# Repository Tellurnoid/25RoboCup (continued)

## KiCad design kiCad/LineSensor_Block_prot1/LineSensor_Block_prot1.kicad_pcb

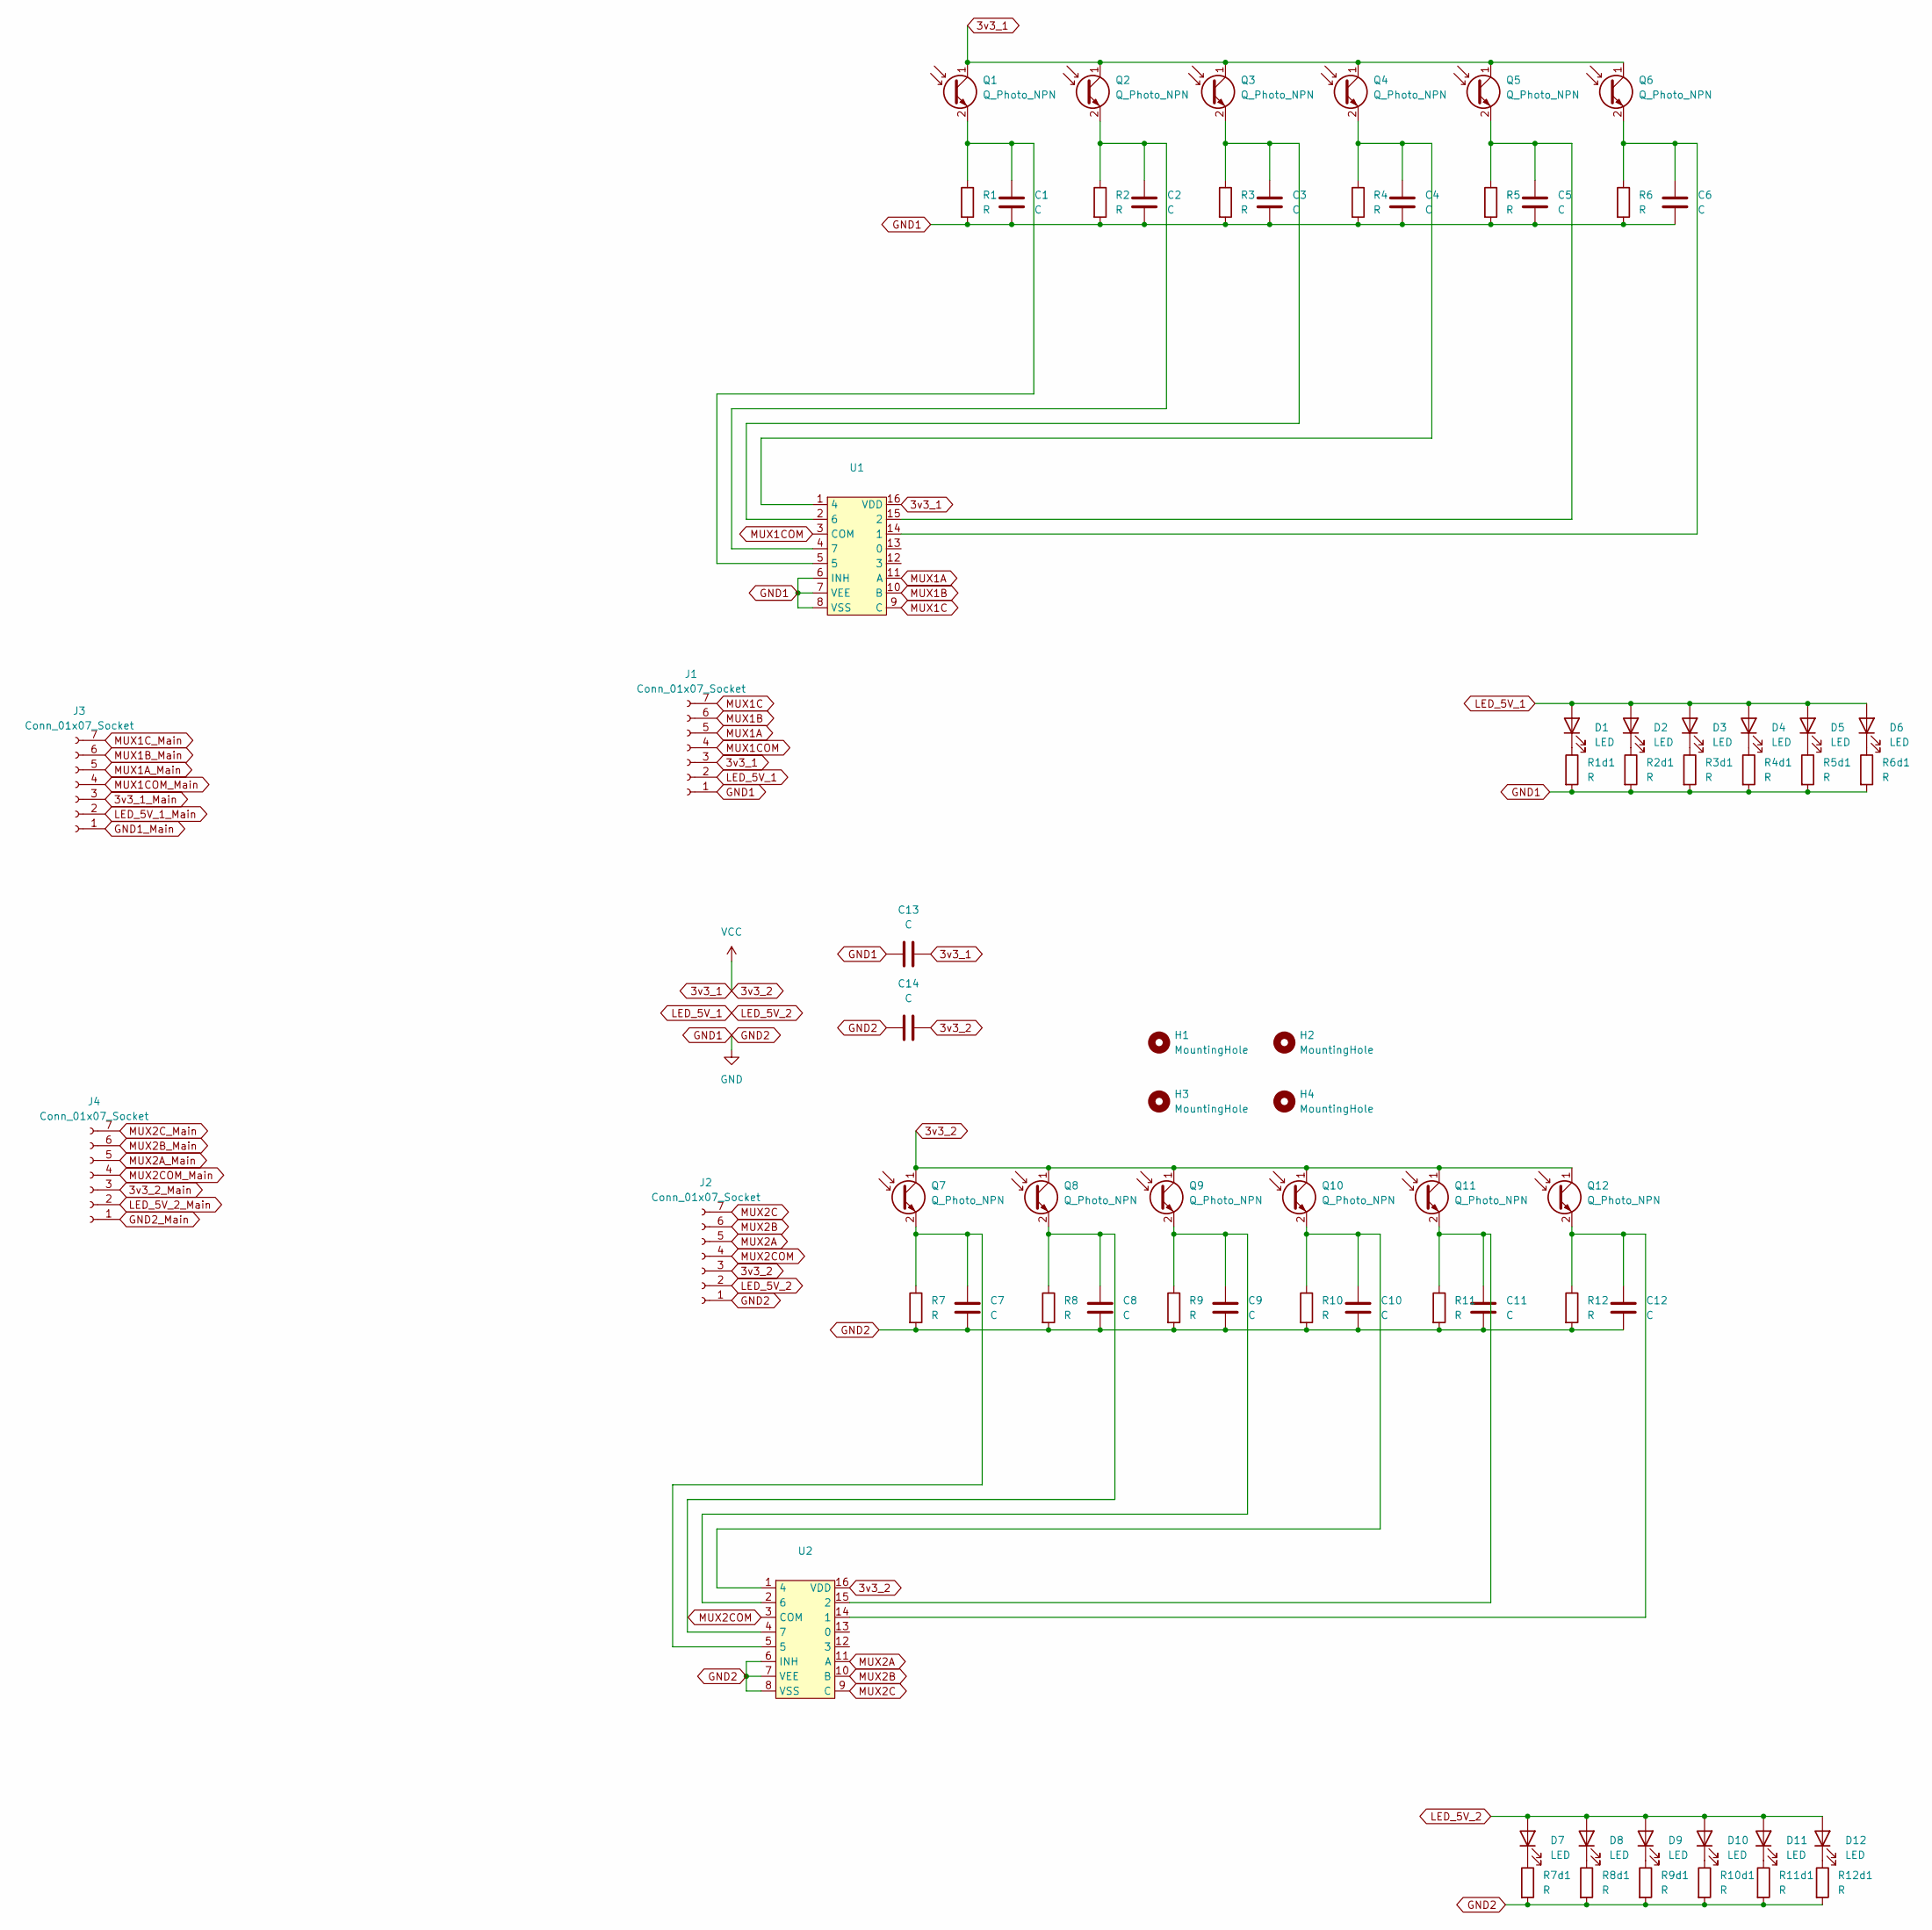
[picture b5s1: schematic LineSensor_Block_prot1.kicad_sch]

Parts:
C1, C2, C3, C4, C5, C6, C8, C9, C10, C11, C12, C13, C14: C; C_0603_1608Metric
C7: C; R_0603_1608Metric
D1, D2, D3, D4, D5, D6, D7, D8, D9, D10, D11, D12: LED; LED_0603_1608Metric
H1, H2, H3, H4: MountingHole; MountingHole_3.2mm_M3
J1, J2: Conn_01x07_Socket; PinHeader_1x07_P2.54mm_Horizontal_edited
J3, J4: Conn_01x07_Socket; PinSocket_1x07_P2.54mm_Horizontal_edited
Q1, Q2, Q3, Q4, Q5, Q6, Q7, Q8, Q9, Q10, Q11, Q12: Q_Photo_NPN; LED_0603_1608Metric
R1, R1d1, R2, R2d1, R3, R3d1, R4, R4d1, R5, R5d1, R6, R6d1, R7, R7d1, R8, R8d1, R9, R9d1, R10, R10d1, R11, R11d1, R12, R12d1: R; R_0603_1608Metric
U1, U2: TSSOP-16_4.4x5mm_P0.65mm

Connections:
3v3_1: C13.2, C14.2, J1.3, J2.3, Q1.1 (C), Q2.1 (C), Q3.1 (C), Q4.1 (C), Q5.1 (C), Q6.1 (C), Q7.1 (C), Q8.1 (C), Q9.1 (C), Q10.1 (C), Q11.1 (C), Q12.1 (C), U1.16 (VDD), U2.16 (VDD)
3v3_1_Main: J3.3
3v3_2_Main: J4.3
GND1: C1.2, C2.2, C3.2, C4.2, C5.2, C6.2, C7.2, C8.2, C9.2, C10.2, C11.2, C12.2, C13.1, C14.1, J1.1, J2.1, R1.2, R1d1.2, R2.2, R2d1.2, R3.2, R3d1.2, R4.2, R4d1.2, R5.2, R5d1.2, R6.2, R6d1.2, R7.2, R7d1.2, R8.2, R8d1.2, R9.2, R9d1.2, R10.2, R10d1.2, R11.2, R11d1.2, R12.2, R12d1.2, U1.6 (INH), U1.7 (VEE), U1.8 (VSS), U2.6 (INH), U2.7 (VEE), U2.8 (VSS)
GND1_Main: J3.1
GND2_Main: J4.1
LED_5V_1: D1.2 (A), D2.2 (A), D3.2 (A), D4.2 (A), D5.2 (A), D6.2 (A), D7.2 (A), D8.2 (A), D9.2 (A), D10.2 (A), D11.2 (A), D12.2 (A), J1.2, J2.2
LED_5V_1_Main: J3.2
LED_5V_2_Main: J4.2
MUX1A: J1.5, U1.11 (A)
MUX1A_Main: J3.5
MUX1B: J1.6, U1.10 (B)
MUX1B_Main: J3.6
MUX1C: J1.7, U1.9 (C)
MUX1COM: J1.4, U1.3 (COM)
MUX1COM_Main: J3.4
MUX1C_Main: J3.7
MUX2A: J2.5, U2.11 (A)
MUX2A_Main: J4.5
MUX2B: J2.6, U2.10 (B)
MUX2B_Main: J4.6
MUX2C: J2.7, U2.9 (C)
MUX2COM: J2.4, U2.3 (COM)
MUX2COM_Main: J4.4
MUX2C_Main: J4.7
unnamed: D1.1 (K), R1d1.1
unnamed: D2.1 (K), R2d1.1
unnamed: D3.1 (K), R3d1.1
unnamed: D4.1 (K), R4d1.1
unnamed: D5.1 (K), R5d1.1
unnamed: D6.1 (K), R6d1.1
unnamed: D7.1 (K), R7d1.1
unnamed: D8.1 (K), R8d1.1
unnamed: D9.1 (K), R9d1.1
unnamed: D10.1 (K), R10d1.1
unnamed: D11.1 (K), R11d1.1
unnamed: D12.1 (K), R12d1.1
unnamed: C1.1, Q1.2 (E), R1.1, U1.5
unnamed: C2.1, Q2.2 (E), R2.1, U1.4 (7)
unnamed: C3.1, Q3.2 (E), R3.1, U1.2 (6)
unnamed: C4.1, Q4.2 (E), R4.1, U1.1 (4)
unnamed: C5.1, Q5.2 (E), R5.1, U1.15 (2)
unnamed: C6.1, Q6.2 (E), R6.1, U1.14 (1)
unnamed: C7.1, Q7.2 (E), R7.1, U2.5
unnamed: C8.1, Q8.2 (E), R8.1, U2.4 (7)
unnamed: C9.1, Q9.2 (E), R9.1, U2.2 (6)
unnamed: C10.1, Q10.2 (E), R10.1, U2.1 (4)
unnamed: C11.1, Q11.2 (E), R11.1, U2.15 (2)
unnamed: C12.1, Q12.2 (E), R12.1, U2.14 (1)

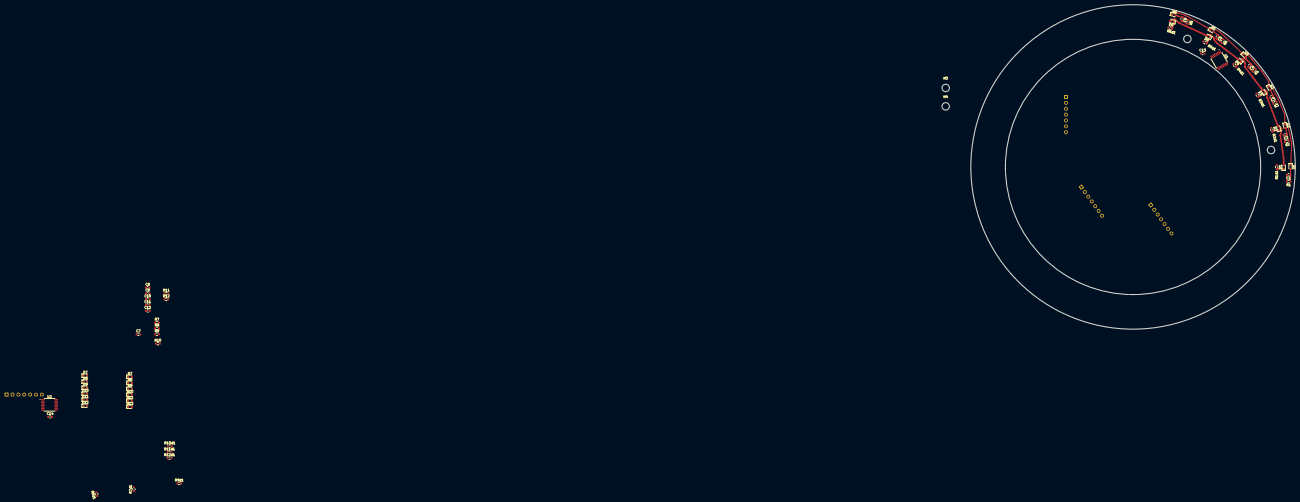
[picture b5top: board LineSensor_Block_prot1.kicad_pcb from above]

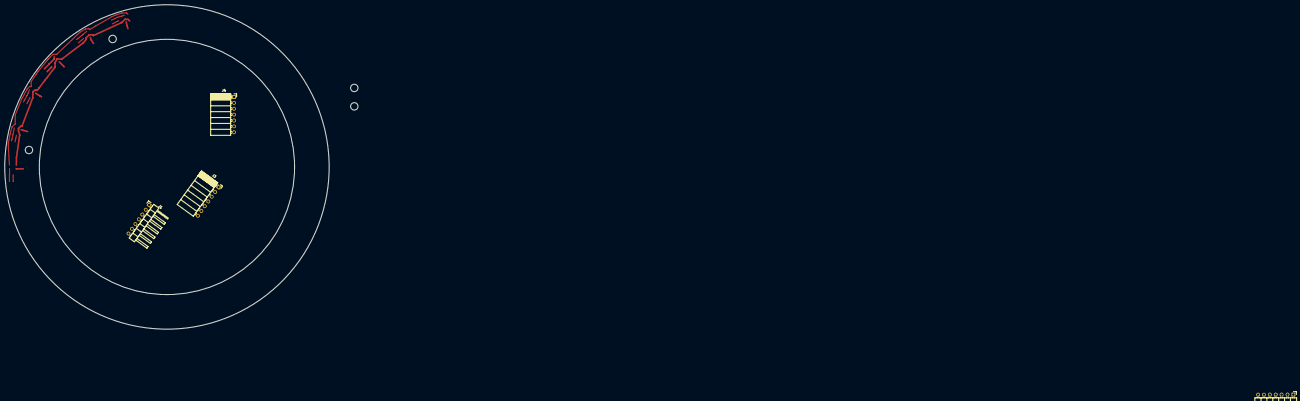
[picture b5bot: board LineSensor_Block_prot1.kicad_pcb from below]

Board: 2 copper layers, 140.0 x 140.0 mm, 72 parts (4 on the bottom side), 35 nets.

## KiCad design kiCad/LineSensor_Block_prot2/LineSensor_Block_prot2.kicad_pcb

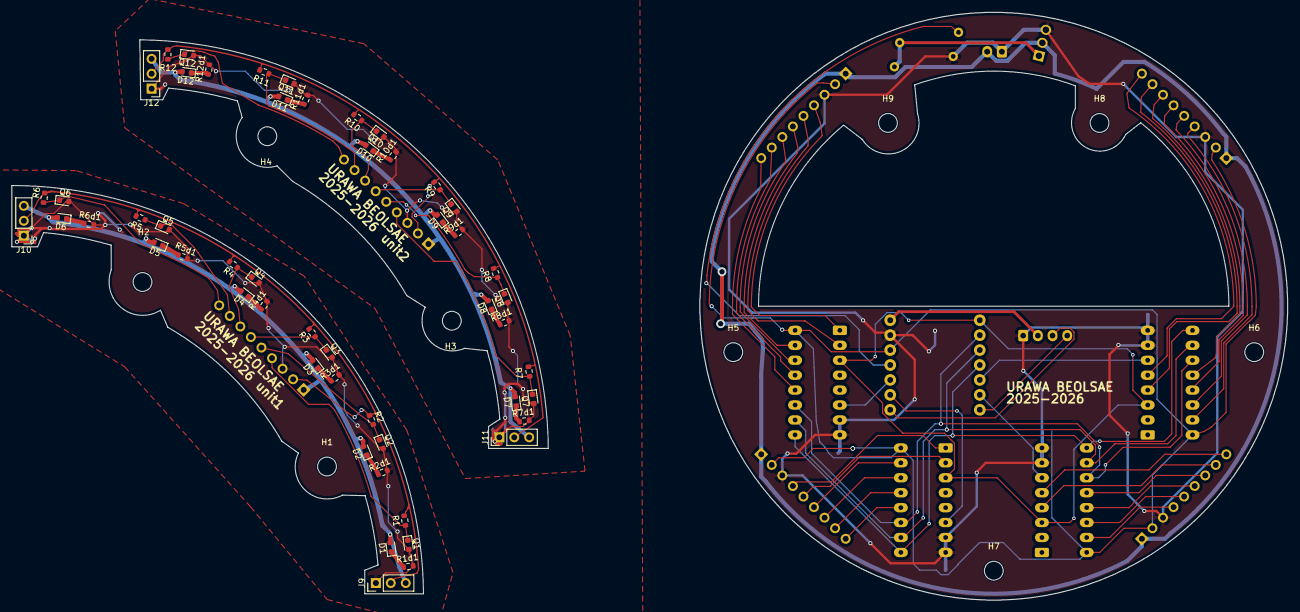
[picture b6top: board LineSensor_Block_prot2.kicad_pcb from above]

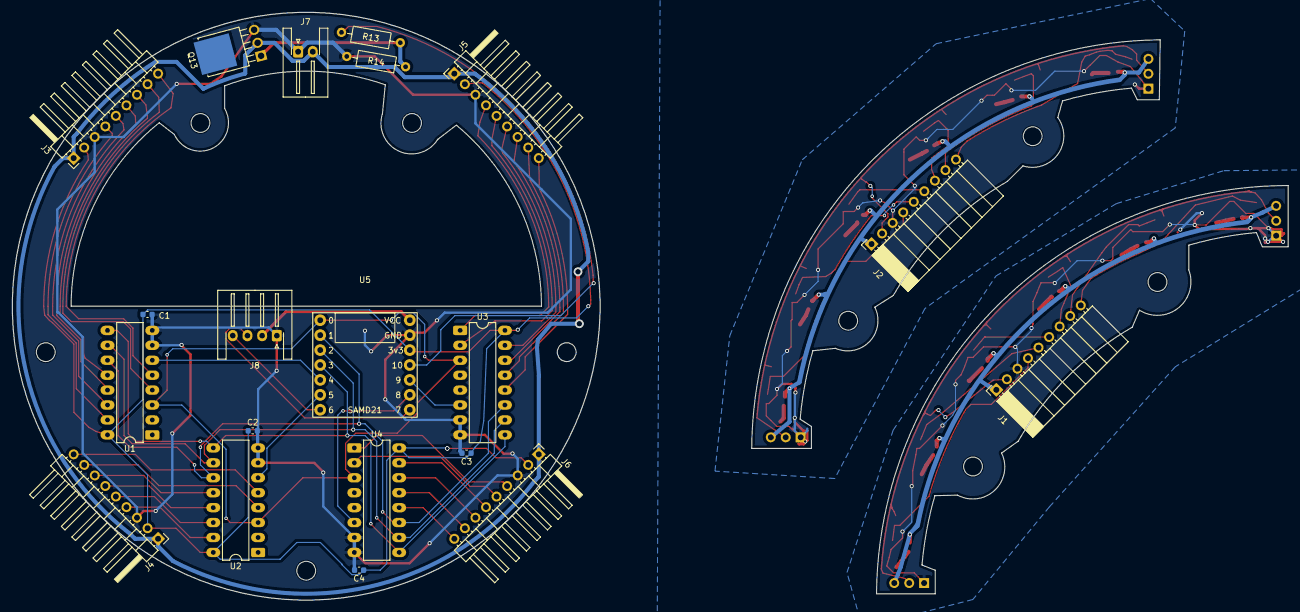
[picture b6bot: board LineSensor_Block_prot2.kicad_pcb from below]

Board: 2 copper layers, 217.1 x 100.0 mm, 81 parts (20 on the bottom side), 70 nets.

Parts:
C1, C2, C3, C4: C; C_0603_1608Metric
D1, D2, D3, D4, D5, D6, D7, D8, D9, D10, D11, D12: LED; LED_0603_1608Metric
H1, H2, H3, H4, H5, H6, H7, H8, H9: MountingHole; MountingHole_3.2mm_M3
J1, J2: Conn_01x09_Socket; PinSocket_1x09_P2.54mm_Horizontal_EDITED
J3, J4, J5, J6: Conn_01x09_Socket; PinHeader_1x09_P2.54mm_Horizontal_EDITED
J7: Conn_01x02_Socket; JST_XH_S2B-XH-A-1_1x02_P2.50mm_Horizontal
J8: Conn_01x04_Socket; JST_XH_S4B-XH-A-1_1x04_P2.50mm_Horizontal
J9, J10, J11, J12: Conn_01x03_Socket; PinHeader_1x03_P2.54mm_Vertical_EDITED
Q1, Q2, Q3, Q4, Q5, Q6, Q7, Q8, Q9, Q10, Q11, Q12: Q_Photo_NPN; LED_0603_1608Metric
Q13: NMOS; TO-251-3-1EP_Horizontal_TabDown
R1, R1d1, R2, R2d1, R3, R3d1, R4, R4d1, R5, R5d1, R6, R6d1, R7, R7d1, R8, R8d1, R9, R9d1, R10, R10d1, R11, R11d1, R12, R12d1: R; R_0603_1608Metric
R13, R14: R; R_Axial_DIN0207_L6.3mm_D2.5mm_P10.16mm_Horizontal
U1, U2, U3, U4: 4051; CERDIP-16_W7.62mm_SideBrazed_LongPads_pin_EDITED
U5: 名称未設定

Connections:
3v3_1: J1.2, J9.2, J10.2, R1.1, R2.1, R3.1, R4.1, R5.1, R6.1
3v3_2: J2.2, J11.2, J12.2, R7.1, R8.1, R9.1, R10.1, R11.1, R12.1
GND: C1.2, C2.2, C3.2, C4.2, J3.3, J4.3, J5.3, J6.3, J7.1, J8.1, Q13.3 (S), R14.2, U1.7 (VEE), U1.8 (VSS), U2.7 (VEE), U2.8 (VSS), U3.7 (VEE), U3.8 (VSS), U4.7 (VEE), U4.8 (VSS), U5.13 (GND)
GND1: J1.3, J9.1, J10.1, Q1.2 (E), Q2.2 (E), Q3.2 (E), Q4.2 (E), Q5.2 (E), Q6.2 (E), R1d1.2, R2d1.2, R3d1.2, R4d1.2, R5d1.2, R6d1.2
GND2: J2.3, J11.1, J12.1, Q7.2 (E), Q8.2 (E), Q9.2 (E), Q10.2 (E), Q11.2 (E), Q12.2 (E), R7d1.2, R8d1.2, R9d1.2, R10d1.2, R11d1.2, R12d1.2
LED_5V: J3.1, J4.1, J5.1, J6.1, J7.2, Q13.1 (D)
LED_5V_1: D1.2 (A), D2.2 (A), D3.2 (A), D4.2 (A), D5.2 (A), D6.2 (A), J1.1, J9.3, J10.3
LED_5V_2: D7.2 (A), D8.2 (A), D9.2 (A), D10.2 (A), D11.2 (A), D12.2 (A), J2.1, J11.3, J12.3
unnamed: D1.1 (K), R1d1.1
unnamed: D2.1 (K), R2d1.1
unnamed: D3.1 (K), R3d1.1
unnamed: D4.1 (K), R4d1.1
unnamed: D5.1 (K), R5d1.1
unnamed: D6.1 (K), R6d1.1
unnamed: D7.1 (K), R7d1.1
unnamed: D8.1 (K), R8d1.1
unnamed: D9.1 (K), R9d1.1
unnamed: D10.1 (K), R10d1.1
unnamed: D11.1 (K), R11d1.1
unnamed: D12.1 (K), R12d1.1
unnamed: J1.4, Q1.1 (C), R1.2
unnamed: J1.5, Q2.1 (C), R2.2
unnamed: J1.6, Q3.1 (C), R3.2
unnamed: J1.7, Q4.1 (C), R4.2
unnamed: J1.8, Q5.1 (C), R5.2
unnamed: J1.9, Q6.1 (C), R6.2
unnamed: J2.4, Q7.1 (C), R7.2
unnamed: J2.5, Q8.1 (C), R8.2
unnamed: J2.6, Q9.1 (C), R9.2
unnamed: J2.7, Q10.1 (C), R10.2
unnamed: J2.8, Q11.1 (C), R11.2
unnamed: J2.9, Q12.1 (C), R12.2
unnamed: J3.4, U1.15 (X2)
unnamed: J3.5, U1.14 (X1)
unnamed: J3.6, U1.13 (X0)
unnamed: J3.7, U1.12 (X3)
unnamed: J3.8, U1.4 (X7)
unnamed: J3.9, U1.5 (X5)
unnamed: J4.4, U2.15 (X2)
unnamed: J4.5, U2.14 (X1)
unnamed: J4.6, U2.13 (X0)
unnamed: J4.7, U2.12 (X3)
unnamed: J4.8, U2.4 (X7)
unnamed: J4.9, U2.5 (X5)
unnamed: J5.4, U3.1 (X4)
unnamed: J5.5, U3.2 (X6)
unnamed: J5.6, U3.15 (X2)
unnamed: J5.7, U3.14 (X1)
unnamed: J5.8, U3.13 (X0)
unnamed: J5.9, U3.12 (X3)
unnamed: J6.4, U4.1 (X4)
unnamed: J6.5, U4.2 (X6)
unnamed: J6.6, U4.15 (X2)
unnamed: J6.7, U4.14 (X1)
unnamed: J6.8, U4.13 (X0)
unnamed: J6.9, U4.12 (X3)
unnamed: Q13.2 (G), R13.1, R14.1
unnamed: U1.11 (A), U2.11 (A), U3.11 (A), U4.11 (A), U5.2 (1)
unnamed: U1.10 (B), U2.10 (B), U3.10 (B), U4.10 (B), U5.3 (2)
unnamed: U1.9 (C), U2.9 (C), U3.9 (C), U4.9 (C), U5.4 (3)
unnamed: U1.6 (Inh), U5.5 (4)
unnamed: U1.3 (X), U2.3 (X), U3.3 (X), U4.3 (X), U5.1 (0)
unnamed: U2.6 (Inh), U5.6 (5)
unnamed: U3.6 (Inh), U5.10 (9)
unnamed: U4.6 (Inh), U5.9 (8)
unnamed: R13.2, U5.11 (10)
RX: J8.3, U5.8 (7)
TX: J8.4, U5.7 (6)
VCC: J8.2, U5.14 (VCC)
seed_3v3: C1.1, C2.1, C3.1, C4.1, J3.2, J4.2, J5.2, J6.2, U1.16 (VDD), U2.16 (VDD), U3.16 (VDD), U4.16 (VDD), U5.12 (3v3)

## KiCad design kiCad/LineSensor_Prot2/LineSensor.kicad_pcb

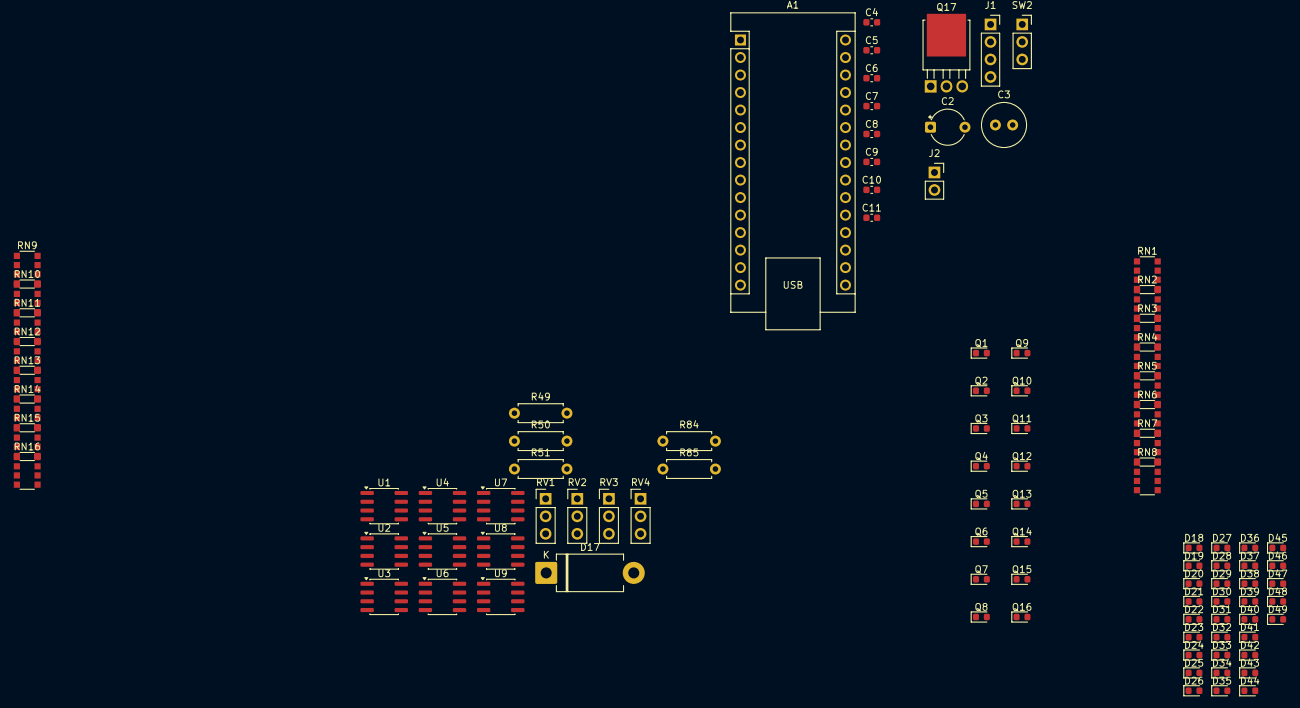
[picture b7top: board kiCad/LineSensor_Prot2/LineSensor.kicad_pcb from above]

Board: 2 copper layers, 98 parts (0 on the bottom side), 78 nets, no tracks yet.

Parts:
A1: Arduino_Nano_v2.x; Arduino_Nano
C2: C; CP_Radial_Tantal_D5.0mm_P5.00mm
C3: C; C_Radial_D6.3mm_H11.0mm_P2.50mm
C4, C5, C6, C7, C8, C9, C10, C11: C; C_0603_1608Metric
D17: D; D_DO-201AD_P12.70mm_Horizontal
D18, D19, D20, D21, D22, D23, D24, D25, D26, D27, D28, D29, D30, D31, D32, D33, D34, D35, D36, D37, D38, D39, D40, D41, D42, D43, D44, D45, D46, D47, D48, D49: LED; LED_0603_1608Metric
J1: Conn_01x04_Socket; PinSocket_1x04_P2.54mm_Vertical
J2: Conn_01x02_Socket; PinSocket_1x02_P2.54mm_Vertical
Q1, Q2, Q3, Q4, Q5, Q6, Q7, Q8, Q9, Q10, Q11, Q12, Q13, Q14, Q15, Q16: Q_Photo_NPN; LED_0603_1608Metric
Q17: NMOS; TO-251-3-1EP_Horizontal_TabDown
R49, R50, R51, R84, R85: R; R_Axial_DIN0207_L6.3mm_D2.5mm_P7.62mm_Horizontal
RN1, RN2, RN3, RN4, RN5, RN6, RN7, RN8, RN9, RN10, RN11, RN12, RN13, RN14, RN15, RN16: R_Network04; R_Array_Convex_4x1206
RV1, RV2, RV3, RV4: R_Potentiometer_Trim; PinHeader_1x03_P2.54mm_Vertical
SW2: SW_DPST_x2; PinSocket_1x03_P2.54mm_Vertical
U1, U2, U3, U4, U5, U6, U7, U8, U9: LM393; SOIC-8_3.9x4.9mm_P1.27mm

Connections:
GND: A1.4 (GND), A1.29 (GND), C2.1, C3.2, C4.2, C5.2, C6.2, C7.2, C8.2, C9.2, C10.2, C11.2, D17.1 (K), J1.3, J2.2, Q17.3 (S), R50.2, R85.1, RN13.1 (common), RN14.1 (common), RN15.1 (common), RN16.1 (common), RV1.3, RV2.3, RV3.3, RV4.3, U2.8 (V+), U3.8 (V+), U4.8 (V+), U5.8 (V+), U6.4 (V-), U7.4 (V-), U8.4 (V-), U9.4 (V-)
unnamed: A1.19 (A0), RN10.5 (R4), U8.7
unnamed: A1.20 (A1), RN10.4 (R3), U8.1
unnamed: A1.21 (A2), RN10.3 (R2), U7.7
unnamed: A1.22 (A3), RN10.2 (R1), U7.1
unnamed: A1.23 (A4), RN9.5 (R4), U2.7
unnamed: A1.2 (D0/RX), J1.2
unnamed: A1.1 (D1/TX), R49.2
unnamed: A1.5 (D2), RN11.2 (R1), U6.7
unnamed: A1.6 (D3), RN11.3 (R2), U6.1
unnamed: A1.7 (D4), RN11.4 (R3), U5.7
unnamed: A1.8 (D5), RN11.5 (R4), U5.1
unnamed: A1.9 (D6), RN12.2 (R1), U3.1
unnamed: A1.10 (D7), RN12.3 (R2), U3.7
unnamed: A1.11 (D8), RN12.4 (R3), U4.1
unnamed: A1.12 (D9), RN12.5 (R4), U4.7
unnamed: A1.13 (D10), R84.1
unnamed: A1.14 (D11), RN9.2 (R1), U1.1
unnamed: A1.15 (D12), RN9.3 (R2), U1.7
unnamed: A1.16 (D13), RN9.4 (R3), U2.1
unnamed: D18.1 (K), RN1.5 (R4)
unnamed: D19.1 (K), RN1.4 (R3)
unnamed: D20.1 (K), RN1.3 (R2)
unnamed: D21.1 (K), RN1.2 (R1)
unnamed: D22.1 (K), RN2.5 (R4)
unnamed: D23.1 (K), RN2.4 (R3)
unnamed: D24.1 (K), RN2.3 (R2)
unnamed: D25.1 (K), RN2.2 (R1)
unnamed: D26.1 (K), RN3.5 (R4)
unnamed: D27.1 (K), RN3.4 (R3)
unnamed: D28.1 (K), RN3.3 (R2)
unnamed: D29.1 (K), RN3.2 (R1)
unnamed: D30.1 (K), RN4.5 (R4)
unnamed: D31.1 (K), RN4.4 (R3)
unnamed: D32.1 (K), RN4.3 (R2)
unnamed: D33.1 (K), RN4.2 (R1)
unnamed: D34.1 (K), RN5.5 (R4)
unnamed: D35.1 (K), RN5.4 (R3)
unnamed: D36.1 (K), RN5.3 (R2)
unnamed: D37.1 (K), RN5.2 (R1)
unnamed: D38.1 (K), RN6.5 (R4)
unnamed: D39.1 (K), RN6.4 (R3)
unnamed: D40.1 (K), RN6.3 (R2)
unnamed: D41.1 (K), RN6.2 (R1)
unnamed: D42.1 (K), RN7.5 (R4)
unnamed: D43.1 (K), RN7.4 (R3)
unnamed: D44.1 (K), RN7.3 (R2)
unnamed: D45.1 (K), RN7.2 (R1)
unnamed: D46.1 (K), RN8.5 (R4)
unnamed: D47.1 (K), RN8.4 (R3)
unnamed: D48.1 (K), RN8.3 (R2)
unnamed: D49.1 (K), RN8.2 (R1)
unnamed: J1.1, R49.1, R51.1
unnamed: J2.1, SW2.2 (B)
unnamed: Q1.2 (E), RN15.5 (R4), U3.3 (+)
unnamed: Q2.2 (E), RN15.4 (R3), U3.5 (+)
unnamed: Q3.2 (E), RN15.3 (R2), U4.3 (+)
unnamed: Q4.2 (E), RN15.2 (R1), U4.5 (+)
unnamed: Q5.2 (E), RN13.2 (R1), U8.6 (-)
unnamed: Q6.2 (E), RN13.3 (R2), U8.2 (-)
unnamed: Q7.2 (E), RN13.4 (R3), U7.6 (-)
unnamed: Q8.2 (E), RN13.5 (R4), U7.2 (-)
unnamed: Q9.2 (E), RN16.5 (R4), U6.5 (+)
unnamed: Q10.2 (E), RN16.4 (R3), U6.3 (+)
unnamed: Q11.2 (E), RN16.3 (R2), U5.5 (+)
unnamed: Q12.2 (E), RN16.2 (R1), U5.3 (+)
unnamed: Q13.2 (E), RN14.5 (R4), U1.3 (+)
unnamed: Q14.2 (E), RN14.4 (R3), U1.5 (+)
unnamed: Q15.2 (E), RN14.3 (R2), U2.3 (+)
unnamed: Q16.2 (E), RN14.2 (R1), U2.5 (+)
unnamed: Q17.1 (D), RN1.1 (common), RN2.1 (common), RN3.1 (common), RN4.1 (common), RN5.1 (common), RN6.1 (common), RN7.1 (common), RN8.1 (common)
unnamed: Q17.2 (G), R84.2, R85.2
unnamed: R50.1, R51.2
unnamed: RV4.2, U1.2 (-), U1.6 (-), U2.2 (-), U2.6 (-)
unnamed: RV1.2, U3.2 (-), U3.6 (-), U4.2 (-), U4.6 (-)
unnamed: RV2.2, U5.2 (-), U5.6 (-), U6.2 (-), U6.6 (-)
unnamed: RV3.2, U7.3 (+), U7.5 (+), U8.3 (+), U8.5 (+)
VCC: A1.27 (+5V), C2.2, C3.1, C4.1, C5.1, C6.1, C7.1, C8.1, C9.1, C10.1, C11.1, D17.2 (A), D18.2 (A), D19.2 (A), D20.2 (A), D21.2 (A), D22.2 (A), D23.2 (A), D24.2 (A), D25.2 (A), D26.2 (A), D27.2 (A), D28.2 (A), D29.2 (A), D30.2 (A), D31.2 (A), D32.2 (A), D33.2 (A), D34.2 (A), D35.2 (A), D36.2 (A), D37.2 (A), D38.2 (A), D39.2 (A), D40.2 (A), D41.2 (A), D42.2 (A), D43.2 (A), D44.2 (A), D45.2 (A), D46.2 (A), D47.2 (A), D48.2 (A), D49.2 (A), J1.4, Q1.1 (C), Q2.1 (C), Q3.1 (C), Q4.1 (C), Q5.1 (C), Q6.1 (C), Q7.1 (C), Q8.1 (C), Q9.1 (C), Q10.1 (C), Q11.1 (C), Q12.1 (C), Q13.1 (C), Q14.1 (C), Q15.1 (C), Q16.1 (C), RN9.1 (common), RN10.1 (common), RN11.1 (common), RN12.1 (common), RV1.1, RV2.1, RV3.1, RV4.1, SW2.1 (A), U2.4 (V-), U3.4 (V-), U4.4 (V-), U5.4 (V-), U6.8 (V+), U7.8 (V+), U8.8 (V+), U9.8 (V+)
